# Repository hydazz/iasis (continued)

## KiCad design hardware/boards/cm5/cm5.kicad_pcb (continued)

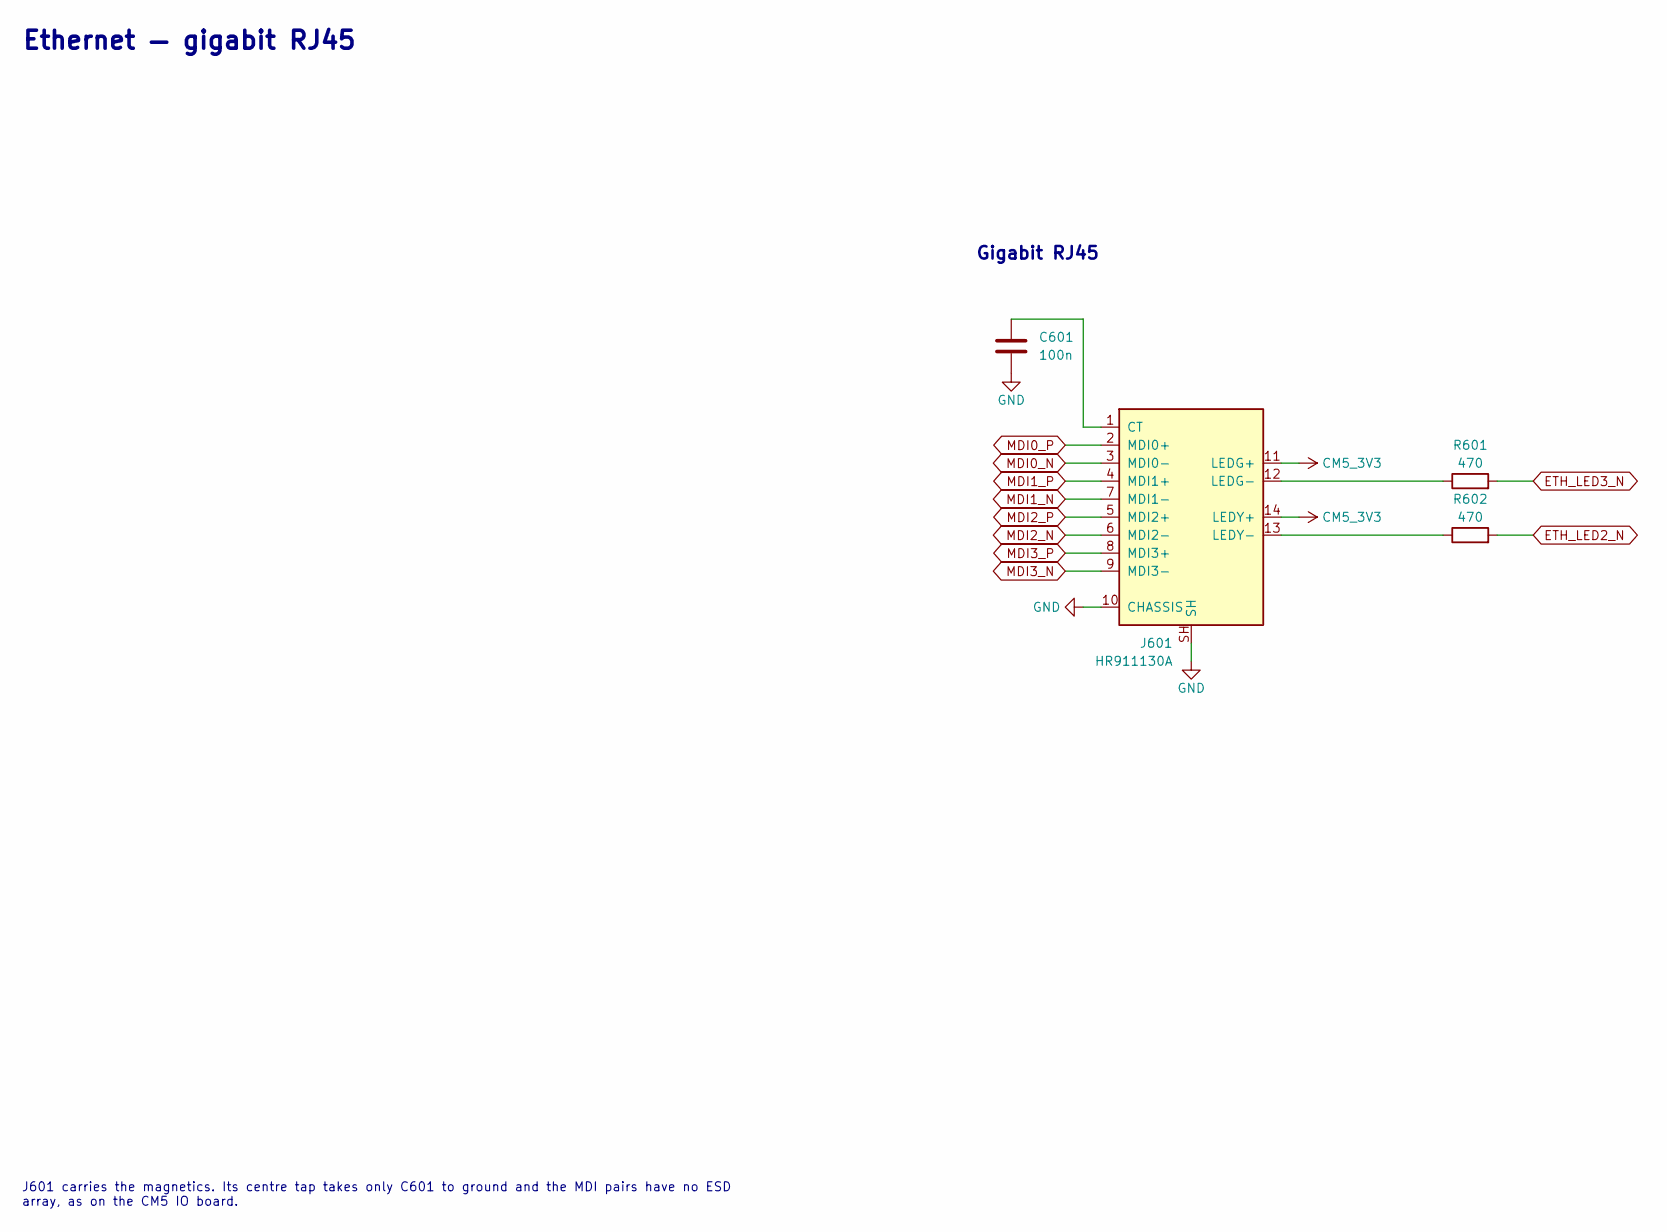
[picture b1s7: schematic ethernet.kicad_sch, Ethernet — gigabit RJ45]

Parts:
C601: 100n; C_0402_1005Metric; MPN CL05B104KO5NNNC; LCSC C1525
J601: HR911130A; HanRun_HR911130A; MPN HR911130A; LCSC C54408
R601, R602: 470; R_0402_1005Metric; MPN 0402WGF4700TCE; LCSC C25117

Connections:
CM5_3V3: J601.11 (LEDG+), J601.14 (LEDY+); also elsewhere on the board
ETH_LED2_N: R602.2; also elsewhere on the board
ETH_LED3_N: R601.2; also elsewhere on the board
GND: C601.2, J601.10 (CHASSIS), J601.SH; also elsewhere on the board
MDI0_N: J601.3 (MDI0-); also elsewhere on the board
MDI0_P: J601.2 (MDI0+); also elsewhere on the board
MDI1_N: J601.7 (MDI1-); also elsewhere on the board
MDI1_P: J601.4 (MDI1+); also elsewhere on the board
MDI2_N: J601.6 (MDI2-); also elsewhere on the board
MDI2_P: J601.5 (MDI2+); also elsewhere on the board
MDI3_N: J601.9 (MDI3-); also elsewhere on the board
MDI3_P: J601.8 (MDI3+); also elsewhere on the board
unnamed: C601.1, J601.1 (CT)
unnamed: J601.12 (LEDG-), R601.1
unnamed: J601.13 (LEDY-), R602.1

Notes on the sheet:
Ethernet — gigabit RJ45
Gigabit RJ45
J601 carries the magnetics. Its centre tap takes only C601 to ground and the MDI pairs have no ESD array, as on the CM5 IO board.

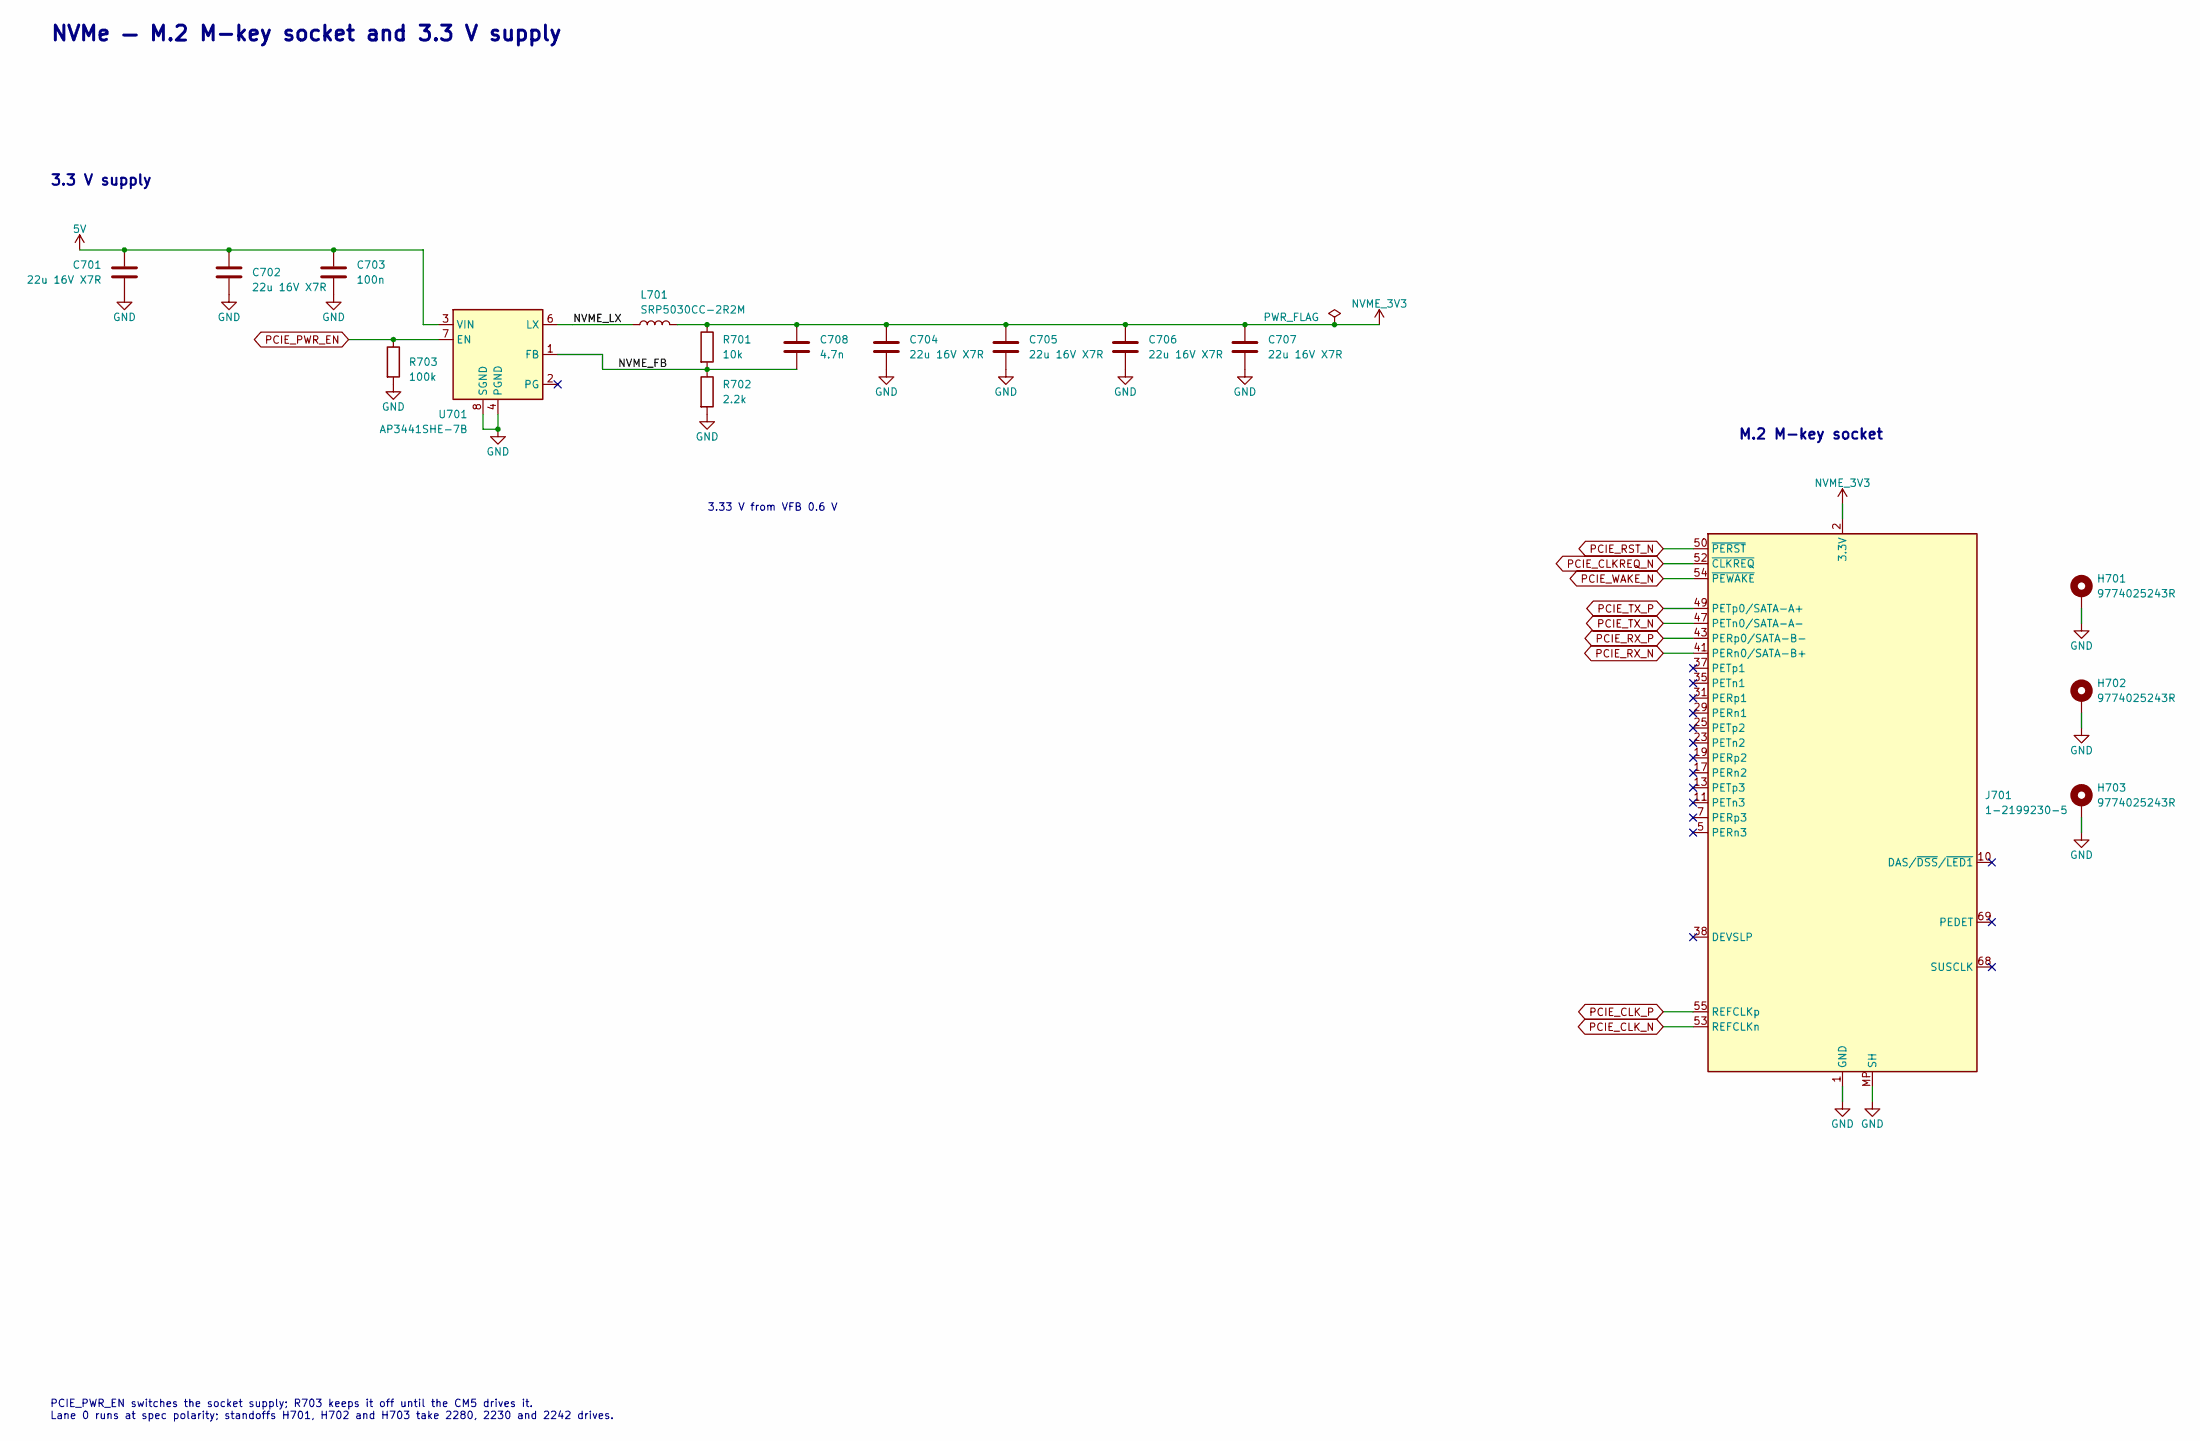
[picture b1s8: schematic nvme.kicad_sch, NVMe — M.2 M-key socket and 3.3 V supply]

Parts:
C701, C702, C704, C705, C706, C707: 22u 16V X7R; C_1210_3225Metric; MPN CL32B226KOJNNNE; LCSC C55530
C703: 100n; C_0402_1005Metric; MPN CL05B104KO5NNNC; LCSC C1525
C708: 4.7n; C_0402_1005Metric; MPN 0402B472K500NT; LCSC C1538
H701, H702, H703: 9774025243R; Mounting_Wuerth_WA-SMSI-M2_H2.5mm_9774025243; MPN 9774025243R; LCSC C22431115
J701: 1-2199230-5; TE_M.2_M_2x38-1MP_P0.5mm; MPN 1-2199230-5; LCSC C590854
L701: SRP5030CC-2R2M; Bourns_SRP5030CC; MPN SRP5030CC-2R2M; LCSC C22404330
R701: 10k; R_0402_1005Metric; MPN 0402WGF1002TCE; LCSC C25744
R702: 2.2k; R_0402_1005Metric; MPN 0402WGF2201TCE; LCSC C25879
R703: 100k; R_0402_1005Metric; MPN 0402WGF1003TCE; LCSC C25741
U701: AP3441SHE-7B; DFN-8-1EP_2x2mm_P0.5mm_EP0.9x1.7mm; MPN AP3441SHE-7B; LCSC C2070918

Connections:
5V: C701.1, C702.1, C703.1, U701.3 (VIN); also elsewhere on the board
/NVMe/NVME_FB: C708.2, R701.2, R702.1, U701.1 (FB)
/NVMe/NVME_LX: L701.1, U701.6 (LX)
GND: C701.2, C702.2, C703.2, C704.2, C705.2, C706.2, C707.2, H701.1 (1_1), H702.1 (1_1), H703.1 (1_1), J701.1 (GND), J701.3 (GND), J701.9 (GND), J701.15 (GND), J701.21 (GND), J701.27 (GND), J701.33 (GND), J701.39 (GND), J701.45 (GND), J701.51 (GND), J701.57 (GND), J701.71 (GND), J701.73 (GND), J701.75 (GND), J701.MP (SH), R702.2, R703.2, U701.4 (PGND), U701.8 (SGND), U701.9 (SGND); also elsewhere on the board
NVME_3V3: C704.1, C705.1, C706.1, C707.1, C708.1, J701.2 (3.3V), J701.4 (3.3V), J701.12 (3.3V), J701.14 (3.3V), J701.16 (3.3V), J701.18 (3.3V), J701.70 (3.3V), J701.72 (3.3V), J701.74 (3.3V), L701.2, R701.1
PCIE_CLKREQ_N: J701.52 (~CLKREQ); also elsewhere on the board
PCIE_CLK_N: J701.53 (REFCLKn); also elsewhere on the board
PCIE_CLK_P: J701.55 (REFCLKp); also elsewhere on the board
PCIE_PWR_EN: R703.1, U701.7 (EN); also elsewhere on the board
PCIE_RST_N: J701.50 (~PERST); also elsewhere on the board
PCIE_RX_N: J701.41 (PERn0/SATA-B+); also elsewhere on the board
PCIE_RX_P: J701.43 (PERp0/SATA-B-); also elsewhere on the board
PCIE_TX_N: J701.47 (PETn0/SATA-A-); also elsewhere on the board
PCIE_TX_P: J701.49 (PETp0/SATA-A+); also elsewhere on the board
PCIE_WAKE_N: J701.54 (~PEWAKE); also elsewhere on the board

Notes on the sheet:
NVMe — M.2 M-key socket and 3.3 V supply
3.3 V supply
M.2 M-key socket
3.33 V from VFB 0.6 V
PCIE_PWR_EN switches the socket supply; R703 keeps it off until the CM5 drives it. Lane 0 runs at spec polarity; standoffs H701, H702 and H703 take 2280, 2230 and 2242 drives.

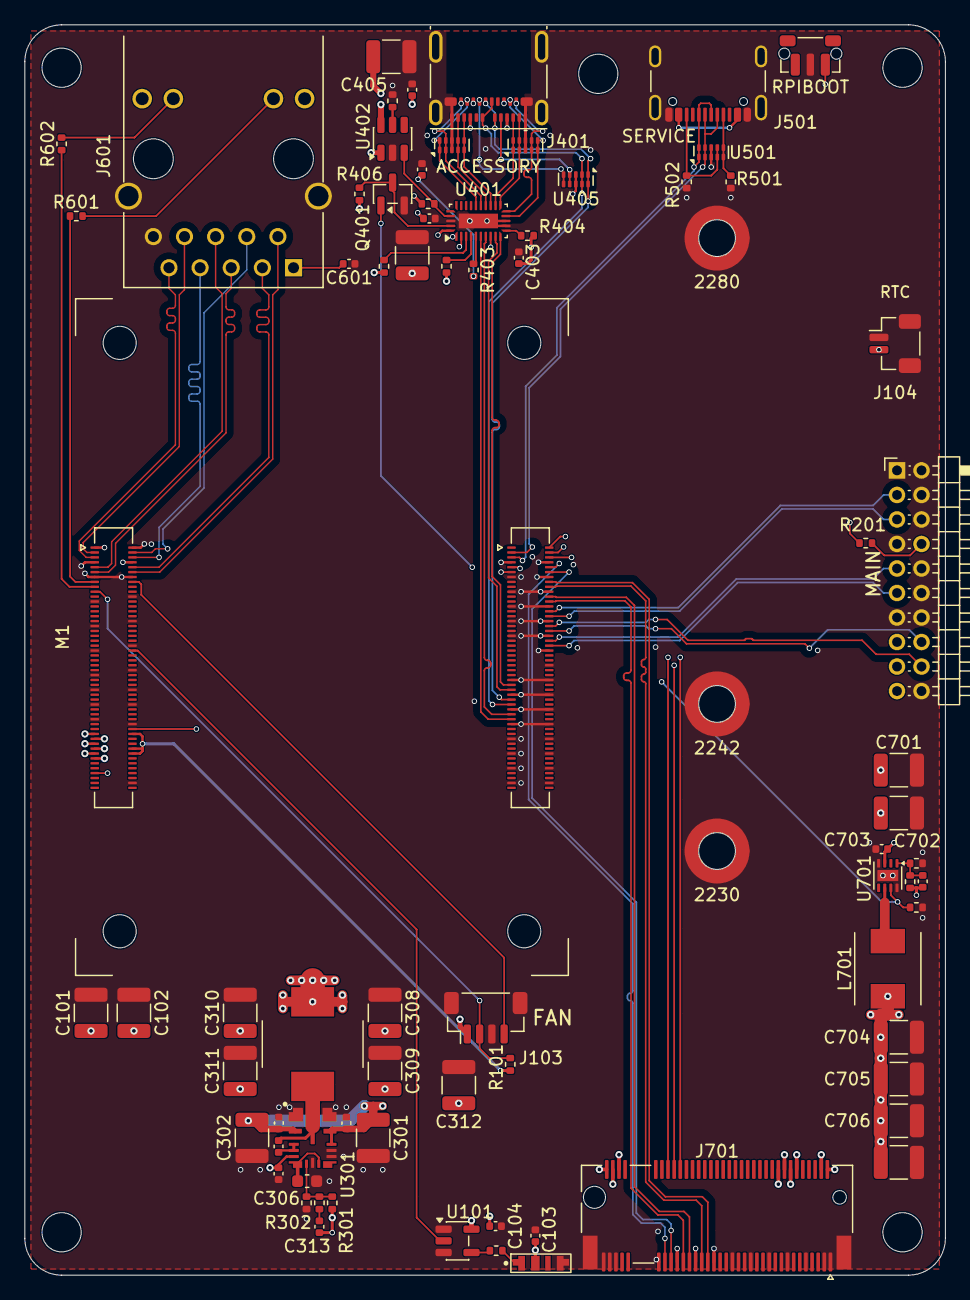
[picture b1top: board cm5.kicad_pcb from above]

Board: 6 copper layers, 75.1 x 102.0 mm, 84 parts (0 on the bottom side), 79 nets.

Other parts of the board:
H1, H2, H3, H4, H5: M3; MountingHole_3.2mm_M3
M1: CM5; RaspberryPi_CM5
